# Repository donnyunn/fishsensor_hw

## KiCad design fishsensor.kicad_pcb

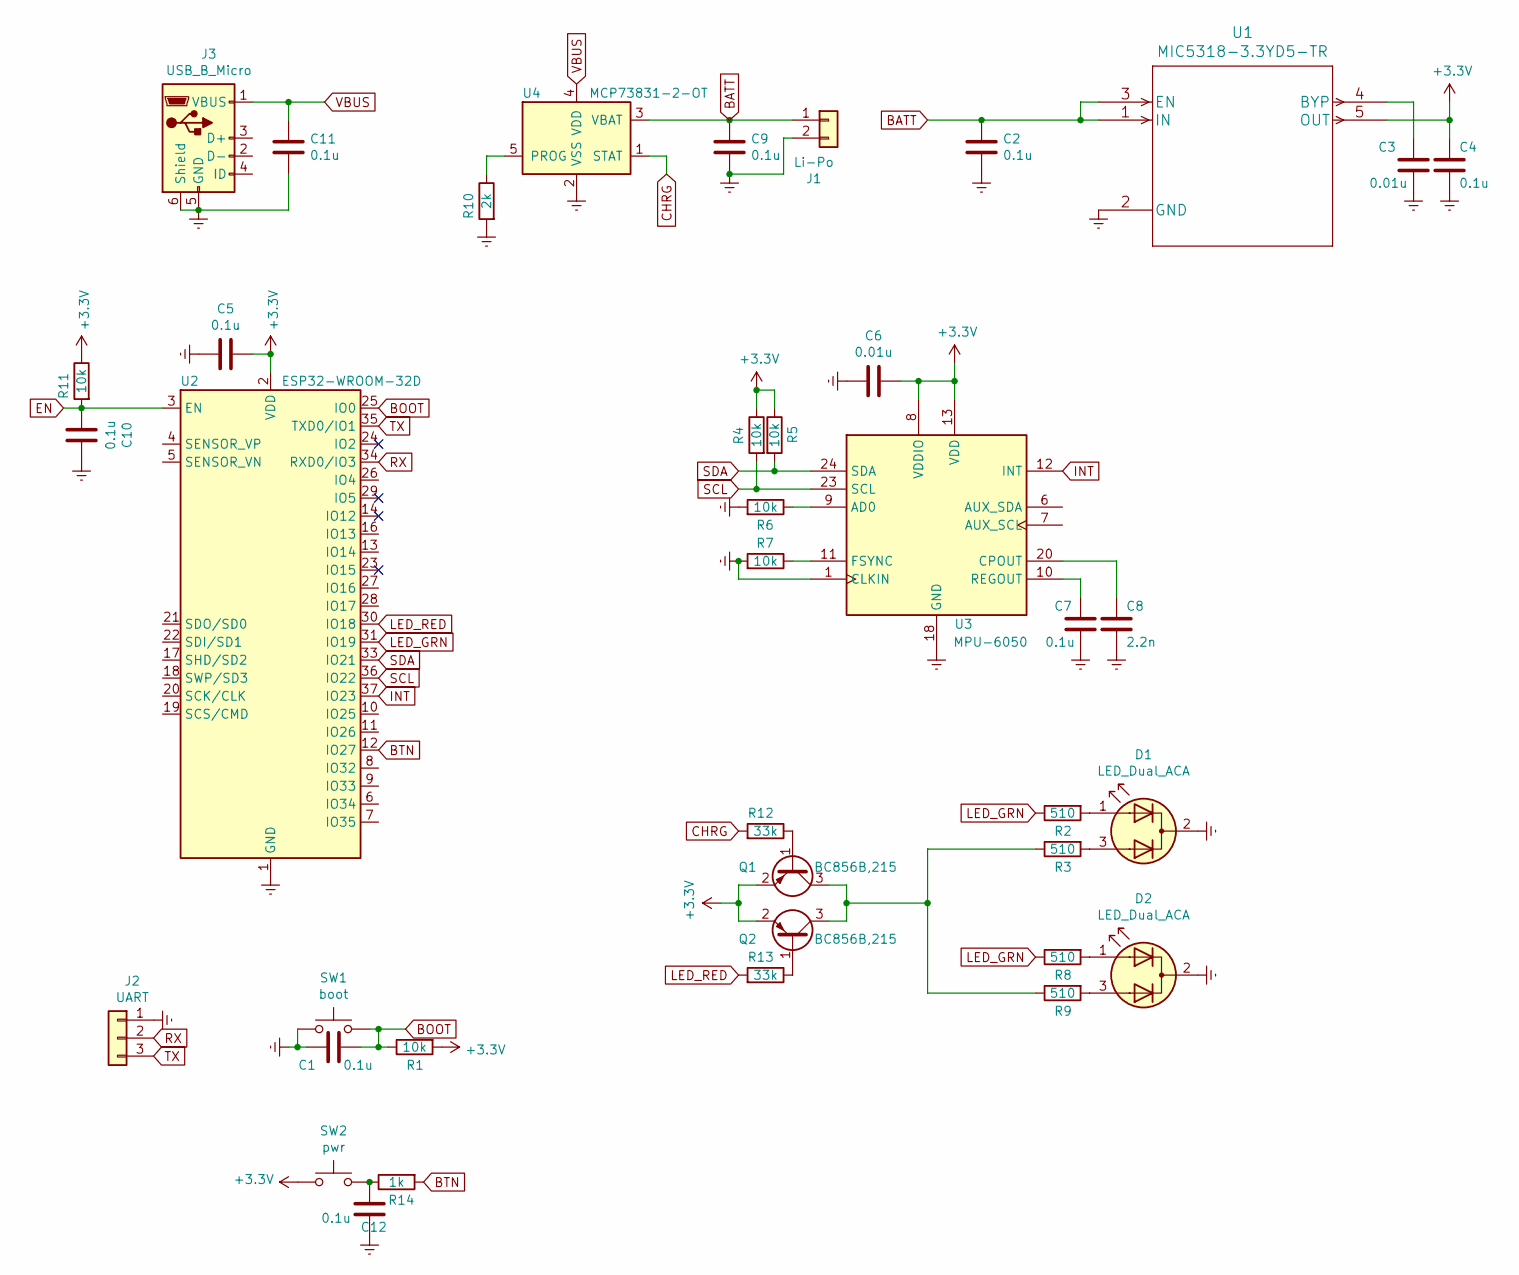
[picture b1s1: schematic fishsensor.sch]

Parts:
C1, C2, C4, C5, C7, C9, C10, C11, C12: 0.1u; C_0603_1608Metric
C3, C6: 0.01u; C_0603_1608Metric
C8: 2.2n; C_0603_1608Metric
D1, D2: LED_Dual_ACA; LED_D5.0mm-3
J1: Li-Po; boot
J2: UART; PinHeader_1x03_P2.54mm_Vertical
J3: USB_B_Micro; USB_Micro-B_GCT_USB3076-30-A
Q1, Q2: BC856B,215; SOT-23; MPN BC856B,215
R1, R4, R5, R6, R7, R11: 10k; R_0603_1608Metric
R2, R3, R8, R9: 510; R_0603_1608Metric
R10: 2k; R_0603_1608Metric
R12, R13: 33k; R_0603_1608Metric
R14: 1k; R_0603_1608Metric
SW1: boot; SW_Push_SPST_NO_Alps_SKRK
SW2: pwr; SW_Push_SPST_NO_Alps_SKRK
U1: MIC5318-3.3YD5-TR; TSOT-23-5
U2: ESP32-WROOM-32D; ESP32-WROOM-32; MPN ESP32-WROOM-32E
U3: MPU-6050; InvenSense_QFN-24_4x4mm_P0.5mm
U4: MCP73831-2-OT; SOT-23-5

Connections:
+3V3: C4.1, C5.2, C6.1, Q1.2 (E), Q2.2 (E), R1.2, R4.1, R5.1, R11.1, SW2.1, U1.5 (OUT), U2.2 (VDD), U3.8 (VDDIO), U3.13 (VDD)
BATT: C2.1, C9.1, J1.1, U1.1 (IN), U1.3 (EN), U4.3 (VBAT)
BOOT: C1.1, R1.1, SW1.2, U2.25 (IO0)
BTN: R14.2, U2.12 (IO27)
CHRG: R12.2, U4.1 (STAT)
EN: C10.1, R11.2, U2.3 (EN)
Earth: C1.2, C2.2, C3.1, C4.2, C5.1, C6.2, C7.1, C8.1, C9.2, C10.2, C11.2, C12.1, D1.2 (K), D2.2 (K), J1.2, J2.1, J3.5 (GND), J3.6 (Shield), R6.2, R7.2, R10.2, SW1.1, U1.2 (GND), U2.1 (GND), U2.15 (GND), U2.38 (GND), U2.39 (GND), U3.1 (CLKIN), U3.18 (GND), U4.2 (VSS)
INT: U2.37 (IO23), U3.12 (INT)
LED_GRN: R2.1, R8.1, U2.31 (IO19)
LED_RED: R13.2, U2.30 (IO18)
unnamed: C3.2, U1.4 (BYP)
unnamed: C7.2, U3.10 (REGOUT)
unnamed: C8.2, U3.20 (CPOUT)
unnamed: C12.2, R14.1, SW2.2
unnamed: D1.1 (A1), R2.2
unnamed: D1.3 (A2), R3.2
unnamed: D2.1 (A1), R8.2
unnamed: D2.3 (A2), R9.2
unnamed: Q1.1 (B), R12.1
unnamed: Q1.3 (C), Q2.3 (C), R3.1, R9.1
unnamed: Q2.1 (B), R13.1
unnamed: R6.1, U3.9 (AD0)
unnamed: R7.1, U3.11 (FSYNC)
unnamed: R10.1, U4.5 (PROG)
RX: J2.2, U2.34 (RXD0/IO3)
SCL: R4.2, U2.36 (IO22), U3.23 (SCL)
SDA: R5.2, U2.33 (IO21), U3.24 (SDA)
TX: J2.3, U2.35 (TXD0/IO1)
VBUS: C11.1, J3.1 (VBUS), U4.4 (VDD)

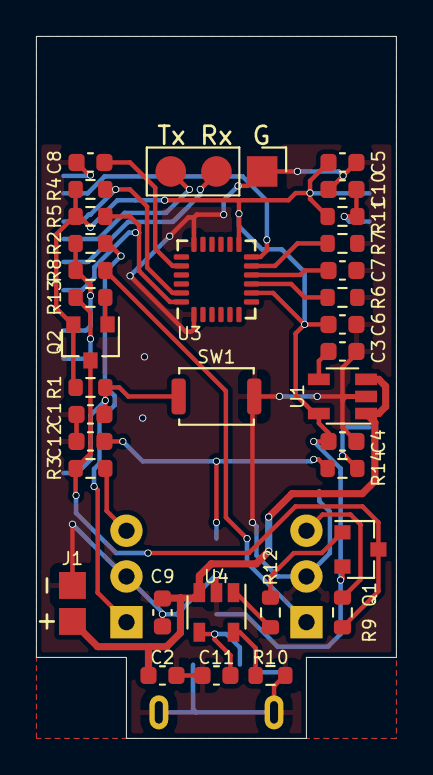
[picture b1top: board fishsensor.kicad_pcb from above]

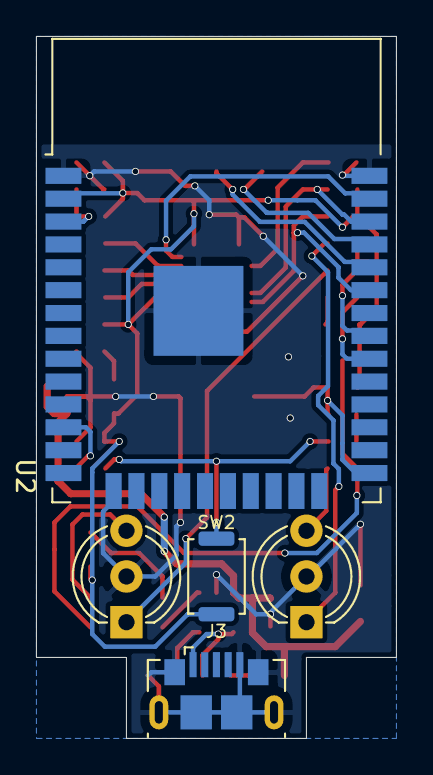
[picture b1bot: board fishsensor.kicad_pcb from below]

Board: 2 copper layers, 20.0 x 39.0 mm, 39 parts (5 on the bottom side), 29 nets.

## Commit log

2021-10-14 2021-10-14
2021-11-04 2021-11-04
